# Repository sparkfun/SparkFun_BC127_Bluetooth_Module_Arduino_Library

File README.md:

SparkFun BC127 Bluetooth Module Arduino Library
==================

<table class="table table-hover table-striped table-bordered">
  <tr>
   <td><a href="https://www.sparkfun.com/products/11927"><div align="center"></div></a></center></td>
   <td><a href="https://www.sparkfun.com/products/11924"><div align="center"></div></a></td>
  </tr>
  <tr>
    <td><div align="center">BC127 Breakout Board [<a href="https://www.sparkfun.com/products/11927">WRL-11927</a>]</div></td>
    <td><div align="center">SparkFun Purpletooth Jamboree - <br/ > BC127 Development Board [<a href="https://www.sparkfun.com/products/11924">WRL-11924</a>]</div></td>
  </tr>
</table>

General purpose Arduino library for the BC127 module by BlueCreation. The Arduino library and example code can be used with the [BC127 Breakout Board](https://www.sparkfun.com/products/11927) and the [PurpleTooth Jamboree](https://www.sparkfun.com/products/11924).

Repository Contents
-------------------

* **/examples** - Example sketches for the library (.ino). Run these from the Arduino IDE. 
* **/src** - Source files for the library (.cpp, .h).
* **keywords.txt** - Keywords from this library that will be highlighted in the Arduino IDE. 
* **library.properties** - General library properties for the Arduino package manager. 

Documentation
--------------

* **[Installing an Arduino Library Guide](https://learn.sparkfun.com/tutorials/installing-an-arduino-library)** - Basic information on how to install an Arduino library.
  * **[BC127 Breakout Board](https://github.com/sparkfun/BC127_Breakout_Board)** - Main repo for the bare BC127 module breakout, including hardware files.
  * **[PurpleTooth Jamboree Repository](https://github.com/sparkfun/Purpletooth_Jamboree)** - Main repo for the PurpleTooth Jamboree, including hardware files.
* **[Hookup Guide](https://learn.sparkfun.com/tutorials/understanding-the-bc127-bluetooth-module)** - Basic hookup guide for the BC127 Breakout Board and PurpleTooth Jamboree.

Products that use this Library 
---------------------------------

* [BC127 Breakout Board](https://www.sparkfun.com/products/11927)- A simple BC127 breakout which exposes all available IO pins to the user.
* [PurpleTooth Jamboree](https://www.sparkfun.com/products/11924)- A BC127-based board with on-board audio signal conditioning hardware.

Version History
---------------

* [V_1.0.0](https://github.com/sparkfun/SparkFun_BC127_Bluetooth_Module_Arduino_Library/releases/tag/V_1.0.0) - Initial release.

License Information
-------------------

This product is _**open source**_! 

The **code** is beerware; if you see me (or any other SparkFun employee) at the local, and you've found our code helpful, please buy us a round!

Please use, reuse, and modify these files as you see fit. Please maintain attribution to SparkFun Electronics and release anything derivative under the same license.

Distributed as-is; no warranty is given.

- Your friends at SparkFun.

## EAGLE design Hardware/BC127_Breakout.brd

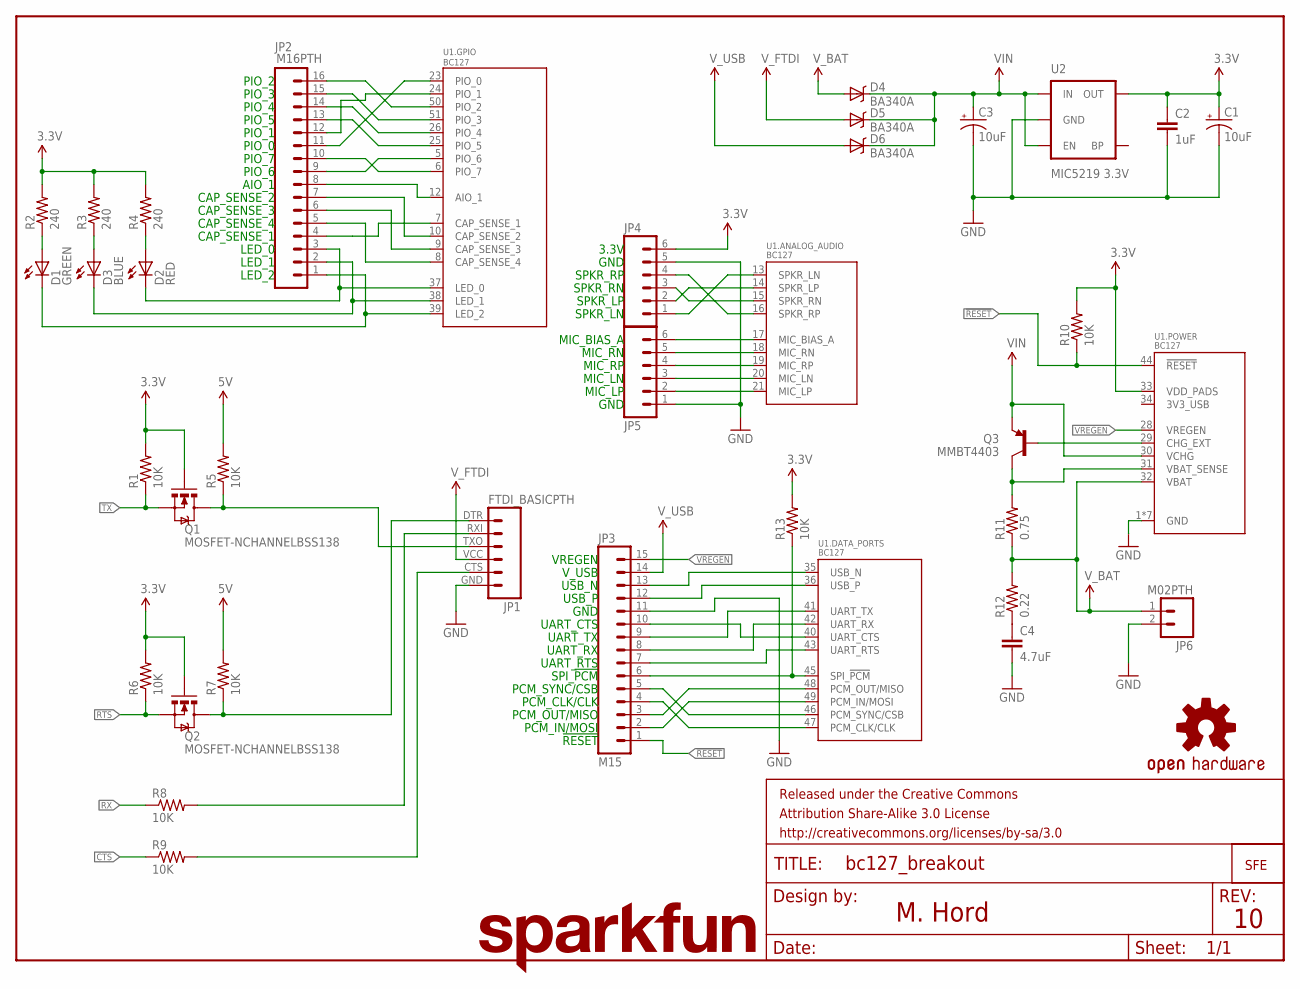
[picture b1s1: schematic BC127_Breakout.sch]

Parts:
C1, C3: 10uF; EIA3216
C2: 1uF; 0805
C4: 4.7uF; 0603-CAP
D1: GREEN; LED-0603
D2: RED; LED-0603
D3: BLUE; LED-0603
D4, D5, D6: BA340A; SMA-DIODE
FRAME1: FRAME-LETTER; CREATIVE_COMMONS
JP1: FTDI_BASICPTH; FTDI_BASIC
JP2: M16PTH; 1X16
JP3: M15; 1X15
JP4, JP5: M06SIP; 1X06
JP6: M02PTH; 1X02
LOGO1: OSHW-LOGOM; OSHW-LOGO-M
LOGO2: LOGO-SFENEW; SFE-NEW-WEBLOGO
LOGO3: SFE_LOGO_NAME.1_INCH; SFE_LOGO_NAME_.1
Q1, Q2: MOSFET-NCHANNELBSS138; SOT23
Q3: MMBT4403; SOT23
R1, R5, R6, R7, R8, R9, R10, R13: 10K; 0603-RES
R2, R3, R4: 240; 0603-RES
R11: 0.75; 0805
R12: 0.22; 0805
U1: BC127; BC127_XTRA_PASTE
U2: MIC5219 3.3V; SOT23-5

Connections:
3.3V: C1.A (+), C2.1, JP4.6, Q1.1 (G), Q2.1 (G), R1.2, R2.2, R3.2, R4.2, R6.2, R10.2, R13.2, U1.33 (VDD_PADS), U2.5 (OUT)
5V_CTS: JP1.CTS (5), R9.2
5V_RTS: JP1.DTR (1), Q2.3 (D), R7.1
5V_RX: JP1.RXI (2), R8.2
5V_TX: JP1.TXO (3), Q1.3 (D), R5.1
!RESET: JP3.1, R10.1, U1.44 (!RESET)
AIO_1: JP2.8, U1.12 (AIO_1)
CAP_SENSE_1: JP2.4, U1.7 (CAP_SENSE_1)
CAP_SENSE_2: JP2.7, U1.10 (CAP_SENSE_2)
CAP_SENSE_3: JP2.6, U1.9 (CAP_SENSE_3)
CAP_SENSE_4: JP2.5, U1.8 (CAP_SENSE_4)
CHG_EXT: Q3.1 (B), U1.29 (CHG_EXT)
CTS: JP3.10, R9.1, U1.40 (UART_CTS)
GND: C1.C (-), C2.2, C3.C (-), C4.2, JP1.GND (6), JP3.11, JP4.5, JP5.1, JP6.2, U1.1 (GND), U1.2 (GND), U1.3 (GND), U1.4 (GND), U1.11 (GND), U1.22 (GND), U1.27 (GND), U2.2 (GND)
LED_0: D2.C, JP2.3, U1.37 (LED_0)
LED_1: D3.C, JP2.2, U1.38 (LED_1)
LED_2: D1.C, JP2.1, U1.39 (LED_2)
MIC_BIAS_A: JP5.6, U1.17 (MIC_BIAS_A)
MIC_LN: JP5.3, U1.20 (MIC_LN)
MIC_LP: JP5.2, U1.21 (MIC_LP)
MIC_RN: JP5.5, U1.18 (MIC_RN)
MIC_RP: JP5.4, U1.19 (MIC_RP)
unnamed: D3.A, R3.1
unnamed: D2.A, R4.1
unnamed: D1.A, R2.1
unnamed: C4.1, R12.1
PCM_CLK/CLK: JP3.4, U1.47 (PCM_CLK/CLK)
PCM_IN/MOSI: JP3.2, U1.49 (PCM_IN/MOSI)
PCM_OUT/MISO: JP3.3, U1.48 (PCM_OUT/MISO)
PCM_SYNC/CSB: JP3.5, U1.46 (PCM_SYNC/CSB)
PIO_0: JP2.11, U1.23 (PIO_0)
PIO_1: JP2.12, U1.24 (PIO_1)
PIO_2: JP2.16, U1.50 (PIO_2)
PIO_3: JP2.15, U1.51 (PIO_3)
PIO_4: JP2.14, U1.26 (PIO_4)
PIO_5: JP2.13, U1.25 (PIO_5)
PIO_6: JP2.9, U1.5 (PIO_6)
PIO_7: JP2.10, U1.6 (PIO_7)
RTS: JP3.7, Q2.2 (S), R6.1, U1.43 (UART_RTS)
RX: JP3.8, R8.1, U1.42 (UART_RX)
SPI_!PCM: JP3.6, R13.1, U1.45 (SPI_!PCM)
SPKR_LN: JP4.1, U1.13 (SPKR_LN)
SPKR_LP: JP4.2, U1.14 (SPKR_LP)
SPKR_RN: JP4.3, U1.15 (SPKR_RN)
SPKR_RP: JP4.4, U1.16 (SPKR_RP)
TX: JP3.9, Q1.2 (S), R1.1, U1.41 (UART_TX)
USB_N: JP3.13, U1.35 (USB_N)
USB_P: JP3.12, U1.36 (USB_P)
VBAT_SENSE: Q3.3 (C), R11.2, U1.31 (VBAT_SENSE)
VIN: C3.A (+), D4.C, D5.C, D6.C, Q3.2 (E), R5.2, R7.2, U1.30 (VCHG), U2.1 (IN), U2.3 (EN)
VREGEN: JP3.15, U1.28 (VREGEN)
V_BAT: D4.A, JP6.1, R11.1, R12.2, U1.32 (VBAT)
V_FTDI: D5.A, JP1.VCC (4)
V_USB: D6.A, JP3.14

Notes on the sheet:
M. Hord
VREGEN
V_USB
USB_N
USB_P
GND
UART_CTS
UART_TX
UART_RX
UART_RTS
SPI_!PCM
PCM_OUT/MISO
PCM_IN/MOSI
PCM_SYNC/CSB
PCM_CLK/CLK
!RESET
MIC_BIAS_A
MIC_RN
MIC_RP
MIC_LN
MIC_LP
SPKR_LN
SPKR_LP
SPKR_RN
SPKR_RP
3.3V
PIO_2
PIO_3
PIO_5
PIO_4
PIO_1
PIO_0
PIO_7
PIO_6
AIO_1
CAP_SENSE_2
CAP_SENSE_3
CAP_SENSE_4
CAP_SENSE_1
LED_0

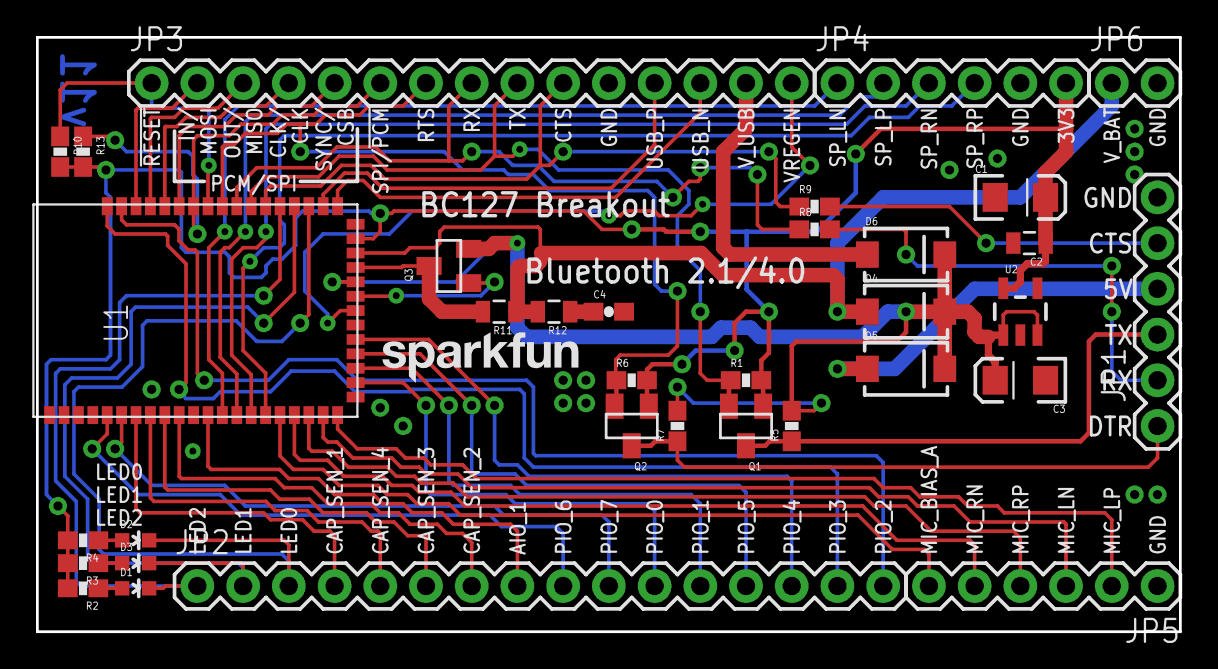
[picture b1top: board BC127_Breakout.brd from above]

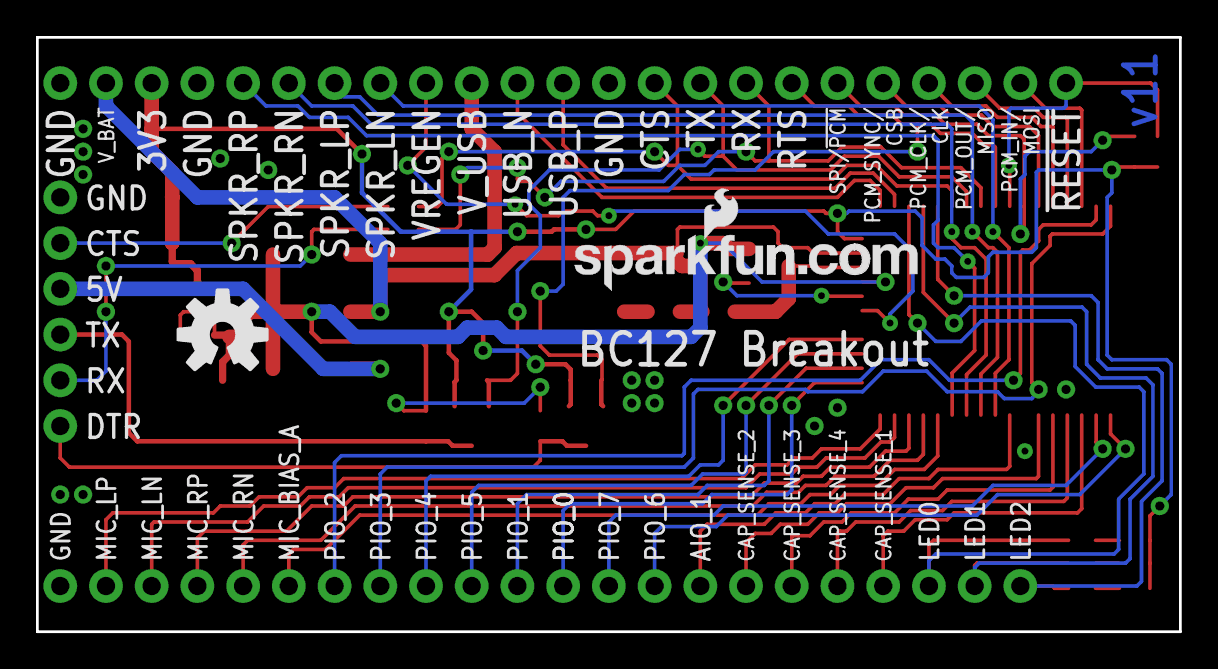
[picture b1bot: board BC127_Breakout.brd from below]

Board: 2 copper layers, 63.5 x 33.0 mm, 38 parts (2 on the bottom side), 54 nets.

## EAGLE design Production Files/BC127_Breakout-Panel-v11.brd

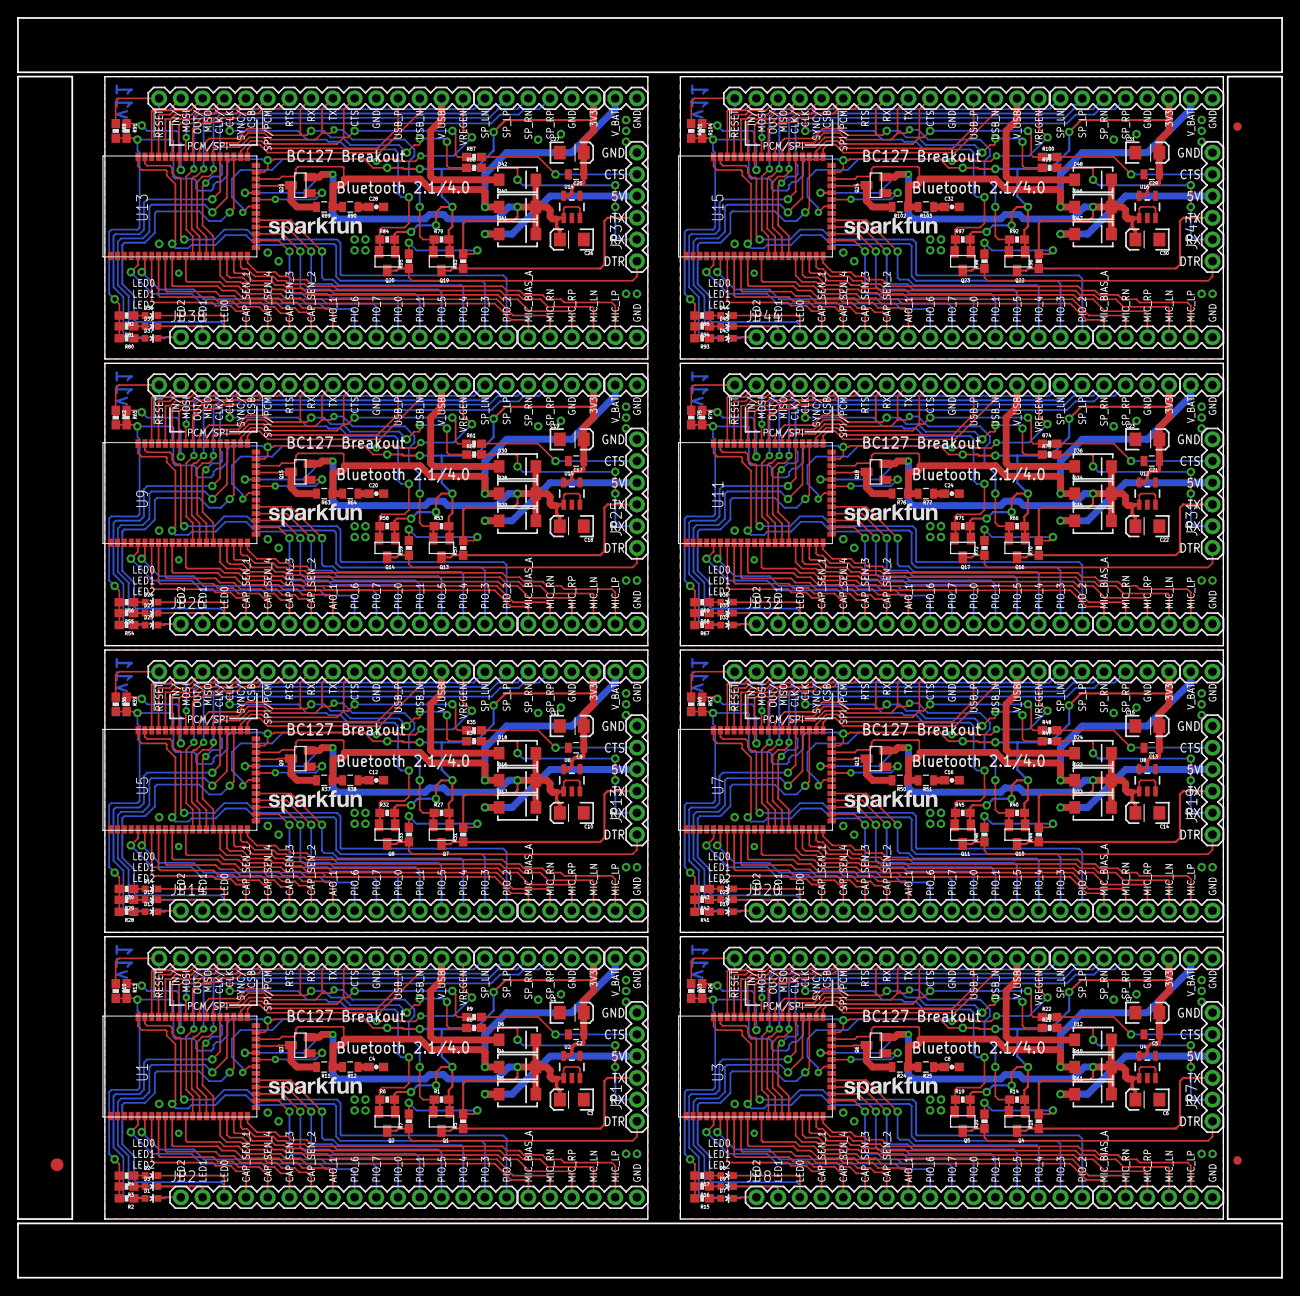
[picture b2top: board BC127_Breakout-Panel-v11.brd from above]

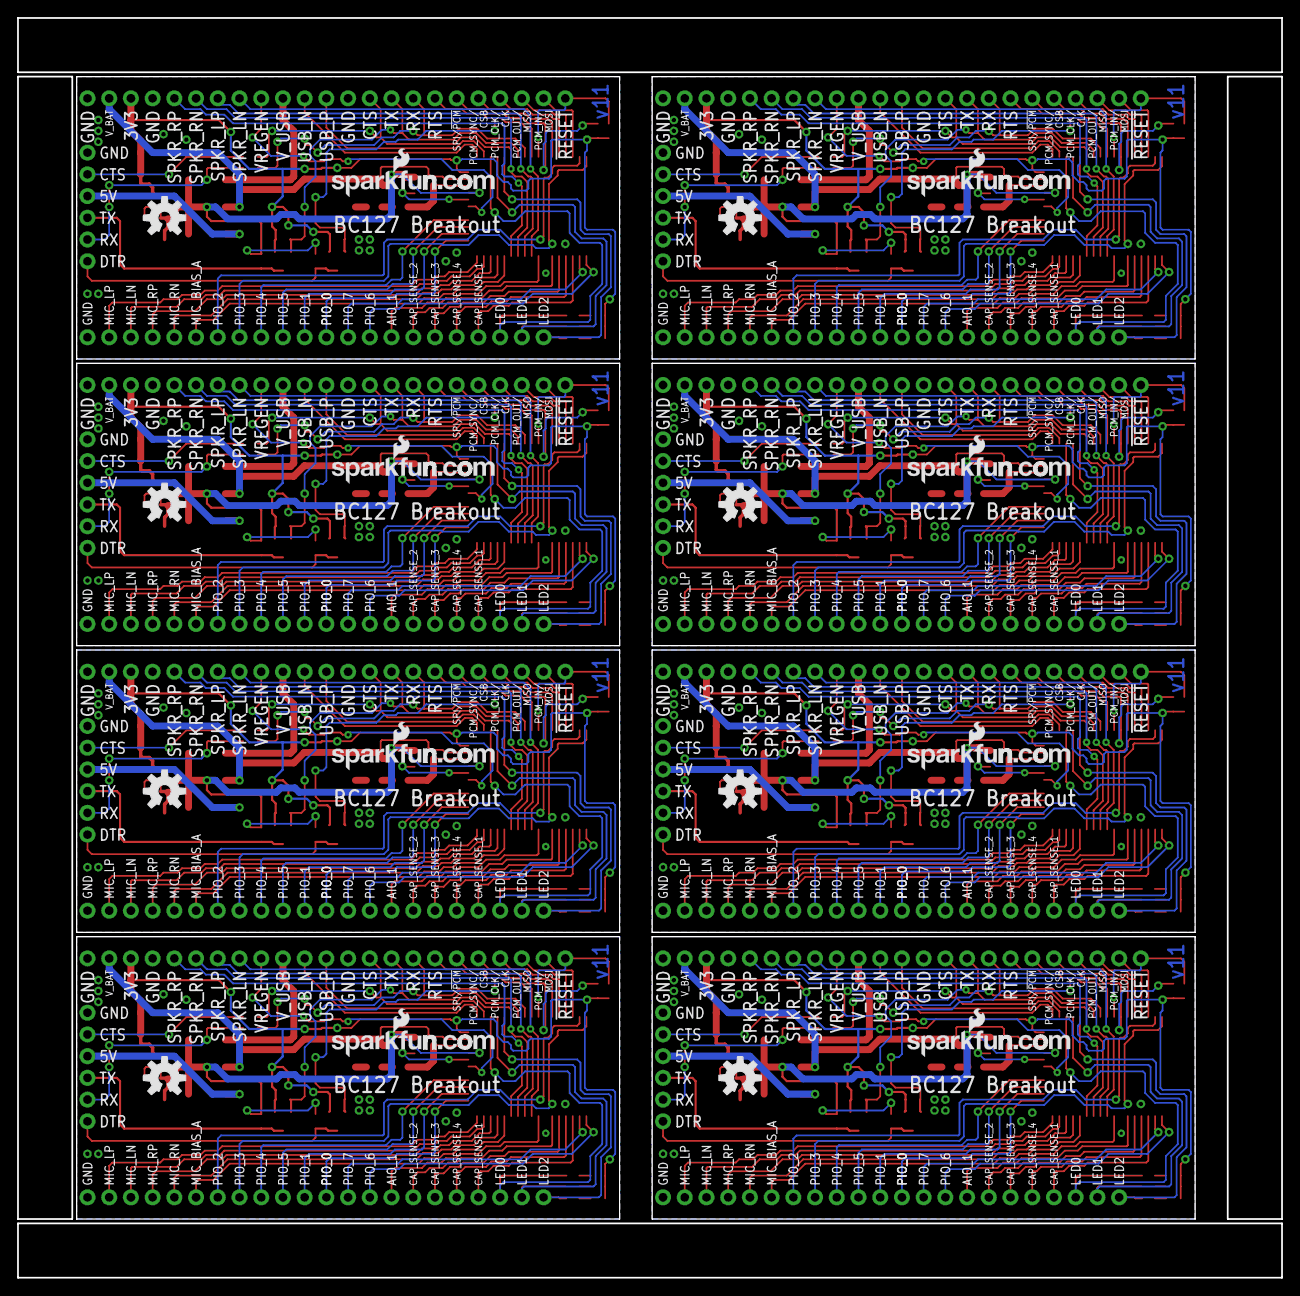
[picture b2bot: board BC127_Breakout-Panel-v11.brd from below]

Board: 2 copper layers, 147.8 x 147.3 mm, 299 parts (16 on the bottom side), 432 nets.

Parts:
C1, C3, C6, C7, C10, C11, C14, C15, C18, C19, C22, C23, C26, C27, C30, C31: 10uF; EIA3216
C2, C5, C9, C13, C17, C21, C25, C29: 1uF; 0805
C4, C8, C12, C16, C20, C24, C28, C32: 4.7uF; 0603-CAP
D1, D7, D13, D19, D25, D31, D37, D43: GREEN; LED-0603
D2, D8, D14, D20, D26, D32, D38, D44: RED; LED-0603
D3, D9, D15, D21, D27, D33, D39, D45: BLUE; LED-0603
D4, D5, D6, D10, D11, D12, D16, D17, D18, D22, D23, D24, D28, D29, D30, D34, D35, D36, D40, D41, D42, D46, D47, D48: BA340A; SMA-DIODE
E$1: FIDUCIAL-1.5X3
E$5, E$6: FIDUCIAL-1X2
JP1, JP7, JP13, JP19, JP25, JP31, JP37, JP43: FTDI_BASICPTH; FTDI_BASIC
JP2, JP8, JP14, JP20, JP26, JP32, JP38, JP44: M16PTH; 1X16
JP3, JP9, JP15, JP21, JP27, JP33, JP39, JP45: M15; 1X15
JP4, JP5, JP10, JP11, JP16, JP17, JP22, JP23, JP28, JP29, JP34, JP35, JP40, JP41, JP46, JP47: 1X06
JP6, JP12, JP18, JP24, JP30, JP36, JP42, JP48: M02PTH; 1X02
LOGO1, LOGO4, LOGO7, LOGO10, LOGO13, LOGO16, LOGO19, LOGO22: OSHW-LOGOM; OSHW-LOGO-M
LOGO2, LOGO5, LOGO8, LOGO11, LOGO14, LOGO17, LOGO20, LOGO23: LOGO-SFENEW; SFE-NEW-WEBLOGO
LOGO3, LOGO6, LOGO9, LOGO12, LOGO15, LOGO18, LOGO21, LOGO24: SFE_LOGO_NAME.1_INCH; SFE_LOGO_NAME_.1
Q1, Q2, Q4, Q5, Q7, Q8, Q10, Q11, Q13, Q14, Q16, Q17, Q19, Q20, Q22, Q23: MOSFET-NCHANNELBSS138; SOT23
Q3, Q6, Q9, Q12, Q15, Q18, Q21, Q24: MMBT4403; SOT23
R1, R5, R6, R7, R8, R9, R10, R13, R14, R18, R19, R20, R21, R22, R23, R26, R27, R31, R32, R33, R34, R35, R36, R39, R40, R44, R45, R46, R47, R48, R49, R52, R53, R57, R58, R59, R60, R61, R62, R65, R66, R70, R71, R72, R73, R74, R75, R78, R79, R83, R84, R85, R86, R87, R88, R91, R92, R96, R97, R98, R99, R100, R101, R104: 10K; 0603-RES
R2, R3, R4, R15, R16, R17, R28, R29, R30, R41, R42, R43, R54, R55, R56, R67, R68, R69, R80, R81, R82, R93, R94, R95: 240; 0603-RES
R11, R24, R37, R50, R63, R76, R89, R102: 0.75; 0805
R12, R25, R38, R51, R64, R77, R90, R103: 0.22; 0805
U1, U3, U5, U7, U9, U11, U13, U15: BC127; BC127_XTRA_PASTE
U2, U4, U6, U8, U10, U12, U14, U16: MIC5219 3.3V; SOT23-5

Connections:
3.3V: C1.A, C2.1, JP4.6, Q1.1, Q2.1, R1.2, R2.2, R3.2, R4.2, R6.2, R10.2, R13.2, U1.33, U2.5
3.3V1: C5.1, C7.A, JP10.6, Q4.1, Q5.1, R14.2, R15.2, R16.2, R17.2, R19.2, R23.2, R26.2, U3.33, U4.5
3.3V2: C9.1, C11.A, JP16.6, Q7.1, Q8.1, R27.2, R28.2, R29.2, R30.2, R32.2, R36.2, R39.2, U5.33, U6.5
3.3V3: C13.1, C15.A, JP22.6, Q10.1, Q11.1, R40.2, R41.2, R42.2, R43.2, R45.2, R49.2, R52.2, U7.33, U8.5
3.3V4: C17.1, C19.A, JP28.6, Q13.1, Q14.1, R53.2, R54.2, R55.2, R56.2, R58.2, R62.2, R65.2, U9.33, U10.5
3.3V5: C21.1, C23.A, JP34.6, Q16.1, Q17.1, R66.2, R67.2, R68.2, R69.2, R71.2, R75.2, R78.2, U11.33, U12.5
3.3V6: C25.1, C27.A, JP40.6, Q19.1, Q20.1, R79.2, R80.2, R81.2, R82.2, R84.2, R88.2, R91.2, U13.33, U14.5
3.3V7: C29.1, C31.A, JP46.6, Q22.1, Q23.1, R92.2, R93.2, R94.2, R95.2, R97.2, R101.2, R104.2, U15.33, U16.5
5V_CTS: JP1.CTS, R9.2
5V_CTS1: JP7.CTS, R22.2
5V_CTS2: JP13.CTS, R35.2
5V_CTS3: JP19.CTS, R48.2
5V_CTS4: JP25.CTS, R61.2
5V_CTS5: JP31.CTS, R74.2
5V_CTS6: JP37.CTS, R87.2
5V_CTS7: JP43.CTS, R100.2
5V_RTS: JP1.DTR, Q2.3, R7.1
5V_RTS1: JP7.DTR, Q5.3, R20.1
5V_RTS2: JP13.DTR, Q8.3, R33.1
5V_RTS3: JP19.DTR, Q11.3, R46.1
5V_RTS4: JP25.DTR, Q14.3, R59.1
5V_RTS5: JP31.DTR, Q17.3, R72.1
5V_RTS6: JP37.DTR, Q20.3, R85.1
5V_RTS7: JP43.DTR, Q23.3, R98.1
5V_RX: JP1.RXI, R8.2
5V_RX1: JP7.RXI, R21.2
5V_RX2: JP13.RXI, R34.2
5V_RX3: JP19.RXI, R47.2
5V_RX4: JP25.RXI, R60.2
5V_RX5: JP31.RXI, R73.2
5V_RX6: JP37.RXI, R86.2
5V_RX7: JP43.RXI, R99.2
5V_TX: JP1.TXO, Q1.3, R5.1
5V_TX1: JP7.TXO, Q4.3, R18.1
5V_TX2: JP13.TXO, Q7.3, R31.1
5V_TX3: JP19.TXO, Q10.3, R44.1
5V_TX4: JP25.TXO, Q13.3, R57.1
5V_TX5: JP31.TXO, Q16.3, R70.1
5V_TX6: JP37.TXO, Q19.3, R83.1
5V_TX7: JP43.TXO, Q22.3, R96.1
!RESET: JP3.1, R10.1, U1.44
!RESET1: JP9.1, R23.1, U3.44
!RESET2: JP15.1, R36.1, U5.44
!RESET3: JP21.1, R49.1, U7.44
!RESET4: JP27.1, R62.1, U9.44
!RESET5: JP33.1, R75.1, U11.44
!RESET6: JP39.1, R88.1, U13.44
!RESET7: JP45.1, R101.1, U15.44
AIO_1: JP2.8, U1.12
AIO_2: JP8.8, U3.12
AIO_3: JP14.8, U5.12
AIO_4: JP20.8, U7.12
AIO_5: JP26.8, U9.12
AIO_6: JP32.8, U11.12
AIO_7: JP38.8, U13.12
AIO_8: JP44.8, U15.12
CAP_SENSE_1: JP2.4, U1.7
CAP_SENSE_2: JP2.7, U1.10
CAP_SENSE_3: JP2.6, U1.9
CAP_SENSE_4: JP2.5, U1.8
CAP_SENSE_5: JP8.6, U3.9
CAP_SENSE_6: JP8.5, U3.8
CAP_SENSE_7: JP8.4, U3.7
CAP_SENSE_8: JP8.7, U3.10
CAP_SENSE_9: JP14.6, U5.9
CAP_SENSE_10: JP14.5, U5.8
CAP_SENSE_11: JP14.4, U5.7
CAP_SENSE_12: JP14.7, U5.10
CAP_SENSE_13: JP20.6, U7.9
CAP_SENSE_14: JP20.5, U7.8
CAP_SENSE_15: JP20.4, U7.7
CAP_SENSE_16: JP20.7, U7.10
CAP_SENSE_17: JP26.6, U9.9
CAP_SENSE_18: JP26.5, U9.8
CAP_SENSE_19: JP26.4, U9.7
CAP_SENSE_20: JP26.7, U9.10
CAP_SENSE_21: JP32.6, U11.9
CAP_SENSE_22: JP32.5, U11.8
CAP_SENSE_23: JP32.4, U11.7
CAP_SENSE_24: JP32.7, U11.10
CAP_SENSE_25: JP38.6, U13.9
CAP_SENSE_26: JP38.5, U13.8
CAP_SENSE_27: JP38.4, U13.7
CAP_SENSE_28: JP38.7, U13.10
CAP_SENSE_29: JP44.6, U15.9
CAP_SENSE_30: JP44.5, U15.8
CAP_SENSE_31: JP44.4, U15.7
CAP_SENSE_32: JP44.7, U15.10
CHG_EXT: Q3.1, U1.29
CHG_EXT1: Q6.1, U3.29
CHG_EXT2: Q9.1, U5.29
CHG_EXT3: Q12.1, U7.29
CHG_EXT4: Q15.1, U9.29
CHG_EXT5: Q18.1, U11.29
CHG_EXT6: Q21.1, U13.29
CHG_EXT7: Q24.1, U15.29
CTS: JP3.10, R9.1, U1.40
CTS1: JP9.10, R22.1, U3.40
CTS2: JP15.10, R35.1, U5.40
CTS3: JP21.10, R48.1, U7.40
CTS4: JP27.10, R61.1, U9.40
CTS5: JP33.10, R74.1, U11.40
CTS6: JP39.10, R87.1, U13.40
CTS7: JP45.10, R100.1, U15.40
GND: C1.C, C2.2, C3.C, C4.2, JP1.GND, JP3.11, JP4.5, JP5.1, JP6.2, U1.1, U1.2, U1.3, U1.4, U1.11, U1.22, U1.27, U2.2
GND1: C5.2, C6.C, C7.C, C8.2, JP7.GND, JP9.11, JP10.5, JP11.1, JP12.2, U3.1, U3.2, U3.3, U3.4, U3.11, U3.22, U3.27, U4.2
GND2: C9.2, C10.C, C11.C, C12.2, JP13.GND, JP15.11, JP16.5, JP17.1, JP18.2, U5.1, U5.2, U5.3, U5.4, U5.11, U5.22, U5.27, U6.2
GND3: C13.2, C14.C, C15.C, C16.2, JP19.GND, JP21.11, JP22.5, JP23.1, JP24.2, U7.1, U7.2, U7.3, U7.4, U7.11, U7.22, U7.27, U8.2
GND4: C17.2, C18.C, C19.C, C20.2, JP25.GND, JP27.11, JP28.5, JP29.1, JP30.2, U9.1, U9.2, U9.3, U9.4, U9.11, U9.22, U9.27, U10.2
GND5: C21.2, C22.C, C23.C, C24.2, JP31.GND, JP33.11, JP34.5, JP35.1, JP36.2, U11.1, U11.2, U11.3, U11.4, U11.11, U11.22, U11.27, U12.2
GND6: C25.2, C26.C, C27.C, C28.2, JP37.GND, JP39.11, JP40.5, JP41.1, JP42.2, U13.1, U13.2, U13.3, U13.4, U13.11, U13.22, U13.27, U14.2
GND7: C29.2, C30.C, C31.C, C32.2, JP43.GND, JP45.11, JP46.5, JP47.1, JP48.2, U15.1, U15.2, U15.3, U15.4, U15.11, U15.22, U15.27, U16.2
LED_0: D2.C, JP2.3, U1.37
LED_1: D3.C, JP2.2, U1.38
LED_2: D1.C, JP2.1, U1.39
LED_3: D7.C, JP8.1, U3.39
LED_4: D9.C, JP8.2, U3.38
LED_5: D8.C, JP8.3, U3.37
LED_6: D13.C, JP14.1, U5.39
LED_7: D15.C, JP14.2, U5.38
LED_8: D14.C, JP14.3, U5.37
LED_9: D19.C, JP20.1, U7.39
LED_10: D21.C, JP20.2, U7.38
LED_11: D20.C, JP20.3, U7.37
LED_12: D25.C, JP26.1, U9.39
LED_13: D27.C, JP26.2, U9.38
LED_14: D26.C, JP26.3, U9.37
LED_15: D31.C, JP32.1, U11.39
LED_16: D33.C, JP32.2, U11.38
LED_17: D32.C, JP32.3, U11.37
LED_18: D37.C, JP38.1, U13.39
LED_19: D39.C, JP38.2, U13.38
LED_20: D38.C, JP38.3, U13.37
LED_21: D43.C, JP44.1, U15.39
LED_22: D45.C, JP44.2, U15.38
LED_23: D44.C, JP44.3, U15.37
MIC_BIAS_A: JP5.6, U1.17
MIC_BIAS_A1: JP11.6, U3.17
MIC_BIAS_A2: JP17.6, U5.17
MIC_BIAS_A3: JP23.6, U7.17
MIC_BIAS_A4: JP29.6, U9.17
MIC_BIAS_A5: JP35.6, U11.17
MIC_BIAS_A6: JP41.6, U13.17
MIC_BIAS_A7: JP47.6, U15.17
MIC_LN: JP5.3, U1.20
MIC_LN1: JP11.3, U3.20
MIC_LN2: JP17.3, U5.20
MIC_LN3: JP23.3, U7.20
MIC_LN4: JP29.3, U9.20
MIC_LN5: JP35.3, U11.20
MIC_LN6: JP41.3, U13.20
MIC_LN7: JP47.3, U15.20
MIC_LP: JP5.2, U1.21
MIC_LP1: JP11.2, U3.21
MIC_LP2: JP17.2, U5.21
MIC_LP3: JP23.2, U7.21
MIC_LP4: JP29.2, U9.21
MIC_LP5: JP35.2, U11.21
MIC_LP6: JP41.2, U13.21
MIC_LP7: JP47.2, U15.21
MIC_RN: JP5.5, U1.18
MIC_RN1: JP11.5, U3.18
MIC_RN2: JP17.5, U5.18
MIC_RN3: JP23.5, U7.18
MIC_RN4: JP29.5, U9.18
MIC_RN5: JP35.5, U11.18
MIC_RN6: JP41.5, U13.18
MIC_RN7: JP47.5, U15.18
MIC_RP: JP5.4, U1.19
MIC_RP1: JP11.4, U3.19
MIC_RP2: JP17.4, U5.19
MIC_RP3: JP23.4, U7.19
MIC_RP4: JP29.4, U9.19
MIC_RP5: JP35.4, U11.19
MIC_RP6: JP41.4, U13.19
MIC_RP7: JP47.4, U15.19
unnamed: D9.A, R16.1
unnamed: D3.A, R3.1
unnamed: D8.A, R17.1
unnamed: D7.A, R15.1
unnamed: C8.1, R25.1
unnamed: D2.A, R4.1
unnamed: D1.A, R2.1
unnamed: D15.A, R29.1
unnamed: D14.A, R30.1
unnamed: D13.A, R28.1
unnamed: C12.1, R38.1
unnamed: D21.A, R42.1
unnamed: D20.A, R43.1
unnamed: D19.A, R41.1
unnamed: C16.1, R51.1
unnamed: D27.A, R55.1
unnamed: D26.A, R56.1
unnamed: D25.A, R54.1
unnamed: C20.1, R64.1
unnamed: D33.A, R68.1
unnamed: D32.A, R69.1
unnamed: D31.A, R67.1
unnamed: C24.1, R77.1
unnamed: D39.A, R81.1
unnamed: D38.A, R82.1
unnamed: D37.A, R80.1
unnamed: C28.1, R90.1
unnamed: C4.1, R12.1
unnamed: D45.A, R94.1
unnamed: D44.A, R95.1
unnamed: D43.A, R93.1
unnamed: C32.1, R103.1
PCM_CLK/CLK: JP3.4, U1.47
PCM_CLK/CLK1: JP9.4, U3.47
PCM_CLK/CLK2: JP15.4, U5.47
PCM_CLK/CLK3: JP21.4, U7.47
PCM_CLK/CLK4: JP27.4, U9.47
PCM_CLK/CLK5: JP33.4, U11.47
PCM_CLK/CLK6: JP39.4, U13.47
PCM_CLK/CLK7: JP45.4, U15.47
PCM_IN/MOSI: JP3.2, U1.49
PCM_IN/MOSI1: JP9.2, U3.49
PCM_IN/MOSI2: JP15.2, U5.49
PCM_IN/MOSI3: JP21.2, U7.49
PCM_IN/MOSI4: JP27.2, U9.49
PCM_IN/MOSI5: JP33.2, U11.49
PCM_IN/MOSI6: JP39.2, U13.49
PCM_IN/MOSI7: JP45.2, U15.49
PCM_OUT/MISO: JP3.3, U1.48
PCM_OUT/MISO1: JP9.3, U3.48
PCM_OUT/MISO2: JP15.3, U5.48
PCM_OUT/MISO3: JP21.3, U7.48
PCM_OUT/MISO4: JP27.3, U9.48
PCM_OUT/MISO5: JP33.3, U11.48
PCM_OUT/MISO6: JP39.3, U13.48
PCM_OUT/MISO7: JP45.3, U15.48
PCM_SYNC/CSB: JP3.5, U1.46
PCM_SYNC/CSB1: JP9.5, U3.46
PCM_SYNC/CSB2: JP15.5, U5.46
PCM_SYNC/CSB3: JP21.5, U7.46
PCM_SYNC/CSB4: JP27.5, U9.46
PCM_SYNC/CSB5: JP33.5, U11.46
PCM_SYNC/CSB6: JP39.5, U13.46
PCM_SYNC/CSB7: JP45.5, U15.46
PIO_0: JP2.11, U1.23
PIO_1: JP2.12, U1.24
PIO_2: JP2.16, U1.50
PIO_3: JP2.15, U1.51
PIO_4: JP2.14, U1.26
PIO_5: JP2.13, U1.25
PIO_6: JP2.9, U1.5
PIO_7: JP2.10, U1.6
PIO_8: JP8.11, U3.23
PIO_9: JP8.13, U3.25
PIO_10: JP8.9, U3.5
PIO_11: JP8.10, U3.6
PIO_12: JP8.14, U3.26
PIO_13: JP8.15, U3.51
PIO_14: JP8.16, U3.50
PIO_15: JP8.12, U3.24
PIO_16: JP14.11, U5.23
PIO_17: JP14.13, U5.25
PIO_18: JP14.9, U5.5
PIO_19: JP14.10, U5.6
PIO_20: JP14.14, U5.26
PIO_21: JP14.15, U5.51
PIO_22: JP14.16, U5.50
PIO_23: JP14.12, U5.24
PIO_24: JP20.11, U7.23
PIO_25: JP20.13, U7.25
PIO_26: JP20.9, U7.5
PIO_27: JP20.10, U7.6
PIO_28: JP20.14, U7.26
PIO_29: JP20.15, U7.51
PIO_30: JP20.16, U7.50
PIO_31: JP20.12, U7.24
PIO_32: JP26.11, U9.23
PIO_33: JP26.13, U9.25
PIO_34: JP26.9, U9.5
PIO_35: JP26.10, U9.6
PIO_36: JP26.14, U9.26
PIO_37: JP26.15, U9.51
PIO_38: JP26.16, U9.50
PIO_39: JP26.12, U9.24
PIO_40: JP32.11, U11.23
PIO_41: JP32.13, U11.25
PIO_42: JP32.9, U11.5
PIO_43: JP32.10, U11.6
PIO_44: JP32.14, U11.26
PIO_45: JP32.15, U11.51
PIO_46: JP32.16, U11.50
PIO_47: JP32.12, U11.24
PIO_48: JP38.11, U13.23
PIO_49: JP38.13, U13.25
PIO_50: JP38.9, U13.5
PIO_51: JP38.10, U13.6
PIO_52: JP38.14, U13.26
PIO_53: JP38.15, U13.51
PIO_54: JP38.16, U13.50
PIO_55: JP38.12, U13.24
PIO_56: JP44.11, U15.23
PIO_57: JP44.13, U15.25
PIO_58: JP44.9, U15.5
PIO_59: JP44.10, U15.6
PIO_60: JP44.14, U15.26
PIO_61: JP44.15, U15.51
PIO_62: JP44.16, U15.50
PIO_63: JP44.12, U15.24
RTS: JP3.7, Q2.2, R6.1, U1.43
RTS1: JP9.7, Q5.2, R19.1, U3.43
RTS2: JP15.7, Q8.2, R32.1, U5.43
RTS3: JP21.7, Q11.2, R45.1, U7.43
RTS4: JP27.7, Q14.2, R58.1, U9.43
RTS5: JP33.7, Q17.2, R71.1, U11.43
RTS6: JP39.7, Q20.2, R84.1, U13.43
RTS7: JP45.7, Q23.2, R97.1, U15.43
RX: JP3.8, R8.1, U1.42
RX1: JP9.8, R21.1, U3.42
RX2: JP15.8, R34.1, U5.42
RX3: JP21.8, R47.1, U7.42
RX4: JP27.8, R60.1, U9.42
RX5: JP33.8, R73.1, U11.42
RX6: JP39.8, R86.1, U13.42
RX7: JP45.8, R99.1, U15.42
SPI_!PCM: JP3.6, R13.1, U1.45
SPI_!PCM1: JP9.6, R26.1, U3.45
SPI_!PCM2: JP15.6, R39.1, U5.45
SPI_!PCM3: JP21.6, R52.1, U7.45
SPI_!PCM4: JP27.6, R65.1, U9.45
SPI_!PCM5: JP33.6, R78.1, U11.45
SPI_!PCM6: JP39.6, R91.1, U13.45
SPI_!PCM7: JP45.6, R104.1, U15.45
SPKR_LN: JP4.1, U1.13
SPKR_LN1: JP10.1, U3.13
SPKR_LN2: JP16.1, U5.13
SPKR_LN3: JP22.1, U7.13
SPKR_LN4: JP28.1, U9.13
SPKR_LN5: JP34.1, U11.13
SPKR_LN6: JP40.1, U13.13
SPKR_LN7: JP46.1, U15.13
SPKR_LP: JP4.2, U1.14
SPKR_LP1: JP10.2, U3.14
SPKR_LP2: JP16.2, U5.14
SPKR_LP3: JP22.2, U7.14
SPKR_LP4: JP28.2, U9.14
SPKR_LP5: JP34.2, U11.14
SPKR_LP6: JP40.2, U13.14
SPKR_LP7: JP46.2, U15.14
SPKR_RN: JP4.3, U1.15
SPKR_RN1: JP10.3, U3.15
SPKR_RN2: JP16.3, U5.15
SPKR_RN3: JP22.3, U7.15
SPKR_RN4: JP28.3, U9.15
SPKR_RN5: JP34.3, U11.15
SPKR_RN6: JP40.3, U13.15
SPKR_RN7: JP46.3, U15.15
SPKR_RP: JP4.4, U1.16
SPKR_RP1: JP10.4, U3.16
SPKR_RP2: JP16.4, U5.16
SPKR_RP3: JP22.4, U7.16
SPKR_RP4: JP28.4, U9.16
SPKR_RP5: JP34.4, U11.16
SPKR_RP6: JP40.4, U13.16
SPKR_RP7: JP46.4, U15.16
TX: JP3.9, Q1.2, R1.1, U1.41
TX1: JP9.9, Q4.2, R14.1, U3.41
TX2: JP15.9, Q7.2, R27.1, U5.41
TX3: JP21.9, Q10.2, R40.1, U7.41
TX4: JP27.9, Q13.2, R53.1, U9.41
TX5: JP33.9, Q16.2, R66.1, U11.41
TX6: JP39.9, Q19.2, R79.1, U13.41
TX7: JP45.9, Q22.2, R92.1, U15.41
USB_N: JP3.13, U1.35
USB_N1: JP9.13, U3.35
USB_N2: JP15.13, U5.35
USB_N3: JP21.13, U7.35
USB_N4: JP27.13, U9.35
USB_N5: JP33.13, U11.35
USB_N6: JP39.13, U13.35
USB_N7: JP45.13, U15.35
USB_P: JP3.12, U1.36
USB_P1: JP9.12, U3.36
USB_P2: JP15.12, U5.36
USB_P3: JP21.12, U7.36
USB_P4: JP27.12, U9.36
USB_P5: JP33.12, U11.36
USB_P6: JP39.12, U13.36
USB_P7: JP45.12, U15.36
VBAT_SENSE: Q3.3, R11.2, U1.31
VBAT_SENSE1: Q6.3, R24.2, U3.31
VBAT_SENSE2: Q9.3, R37.2, U5.31
VBAT_SENSE3: Q12.3, R50.2, U7.31
VBAT_SENSE4: Q15.3, R63.2, U9.31
VBAT_SENSE5: Q18.3, R76.2, U11.31
VBAT_SENSE6: Q21.3, R89.2, U13.31
VBAT_SENSE7: Q24.3, R102.2, U15.31
VIN: C3.A, D4.C, D5.C, D6.C, Q3.2, R5.2, R7.2, U1.30, U2.1, U2.3
VIN1: C6.A, D10.C, D11.C, D12.C, Q6.2, R18.2, R20.2, U3.30, U4.1, U4.3
VIN2: C10.A, D16.C, D17.C, D18.C, Q9.2, R31.2, R33.2, U5.30, U6.1, U6.3
VIN3: C14.A, D22.C, D23.C, D24.C, Q12.2, R44.2, R46.2, U7.30, U8.1, U8.3
VIN4: C18.A, D28.C, D29.C, D30.C, Q15.2, R57.2, R59.2, U9.30, U10.1, U10.3
VIN5: C22.A, D34.C, D35.C, D36.C, Q18.2, R70.2, R72.2, U11.30, U12.1, U12.3
VIN6: C26.A, D40.C, D41.C, D42.C, Q21.2, R83.2, R85.2, U13.30, U14.1, U14.3
VIN7: C30.A, D46.C, D47.C, D48.C, Q24.2, R96.2, R98.2, U15.30, U16.1, U16.3
VREGEN: JP3.15, U1.28
VREGEN1: JP9.15, U3.28
VREGEN2: JP15.15, U5.28
VREGEN3: JP21.15, U7.28
VREGEN4: JP27.15, U9.28
VREGEN5: JP33.15, U11.28
VREGEN6: JP39.15, U13.28
VREGEN7: JP45.15, U15.28
V_BAT: D4.A, JP6.1, R11.1, R12.2, U1.32
V_BAT1: D10.A, JP12.1, R24.1, R25.2, U3.32
V_BAT2: D16.A, JP18.1, R37.1, R38.2, U5.32
V_BAT3: D22.A, JP24.1, R50.1, R51.2, U7.32
V_BAT4: D28.A, JP30.1, R63.1, R64.2, U9.32
V_BAT5: D34.A, JP36.1, R76.1, R77.2, U11.32
V_BAT6: D40.A, JP42.1, R89.1, R90.2, U13.32
V_BAT7: D46.A, JP48.1, R102.1, R103.2, U15.32
V_FTDI: D5.A, JP1.VCC
V_FTDI1: D11.A, JP7.VCC
V_FTDI2: D17.A, JP13.VCC
V_FTDI3: D23.A, JP19.VCC
V_FTDI4: D29.A, JP25.VCC
V_FTDI5: D35.A, JP31.VCC
V_FTDI6: D41.A, JP37.VCC
V_FTDI7: D47.A, JP43.VCC
V_USB: D6.A, JP3.14
V_USB1: D12.A, JP9.14
V_USB2: D18.A, JP15.14
V_USB3: D24.A, JP21.14
V_USB4: D30.A, JP27.14
V_USB5: D36.A, JP33.14
V_USB6: D42.A, JP39.14
V_USB7: D48.A, JP45.14

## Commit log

2013-06-12 Initial commit, pre-review
2013-06-18 Feedback from review implemented. Proto.
2013-09-09 Ready for 2nd protos
2013-10-07 Protos checked out, go for reds.
2013-10-07 created panel, changed from r10 to v10
2013-10-23 Add library and example.
2013-11-20 Final commit for release- library and examples.
2013-12-19 Changed TCream
    -Changed TCream for more paste application to allow for better reflow to
    the BC127 module
2013-12-19 Changed version number on board V11
2014-01-09 removed v10 panel. created v11 panel
2014-01-28 Add license info to library
2015-04-24 Changed file structure
2015-04-27 V_1.0.0 commit, rename and reorg
2015-04-27 Edit readme
2017-12-08 Update README.md
    Place products in a table. Minor markdown edits. Add link to version tag.

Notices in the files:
parts and their libraries:
SparkFun-RF: Licensing: CC v3.0 Share-Alike You are welcome to use this library for commercial purposes.
SparkFun-Aesthetics: Released under the Creative Commons Attribution Share-Alike 3.0 License
SparkFun-Aesthetics: http://creativecommons.org/licenses/by-sa/3.0
